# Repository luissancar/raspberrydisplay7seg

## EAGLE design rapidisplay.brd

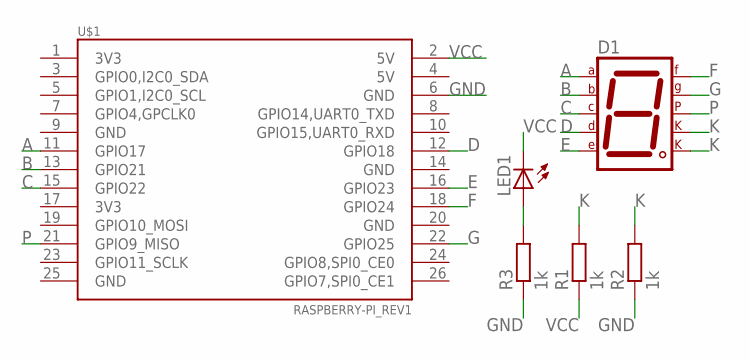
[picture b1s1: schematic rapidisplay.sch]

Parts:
D1: 7SEG-CK; 7SEG-13
LED1: LEDSML1206; SML1206
R1, R2, R3: 1k; M1206
U$1: RASPBERRY-PI_REV1

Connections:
A: D1.7 (A), U$1.11 (GPIO17)
B: D1.6 (B), U$1.13 (GPIO21)
C: D1.4 (C), U$1.15 (GPIO22)
D: D1.2 (D), U$1.12 (GPIO18)
E: D1.1 (E), U$1.16 (GPIO23)
F: D1.9 (F), U$1.18 (GPIO24)
G: D1.10 (G), U$1.22 (GPIO25)
GND: R2.1, R3.1, U$1.6 (GND)
K: D1.3 (CK1), D1.8 (CK2), R1.2, R2.2
unnamed: LED1.A, R3.2
P: D1.5 (DP), U$1.21 (GPIO9_MISO)
VCC: LED1.C, R1.1, U$1.2 (5V)

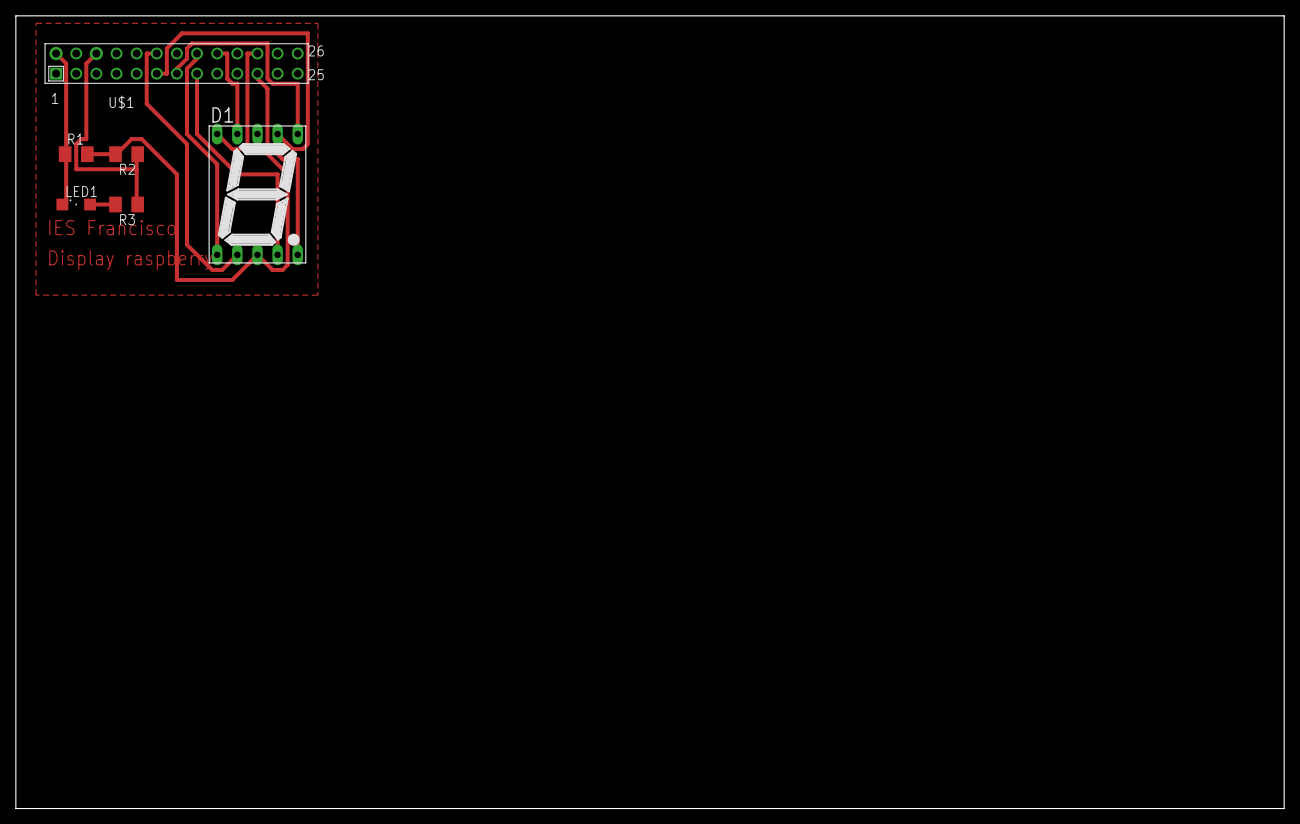
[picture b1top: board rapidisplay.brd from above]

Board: 2 copper layers, 160.0 x 100.0 mm, 6 parts (0 on the bottom side), 12 nets.
